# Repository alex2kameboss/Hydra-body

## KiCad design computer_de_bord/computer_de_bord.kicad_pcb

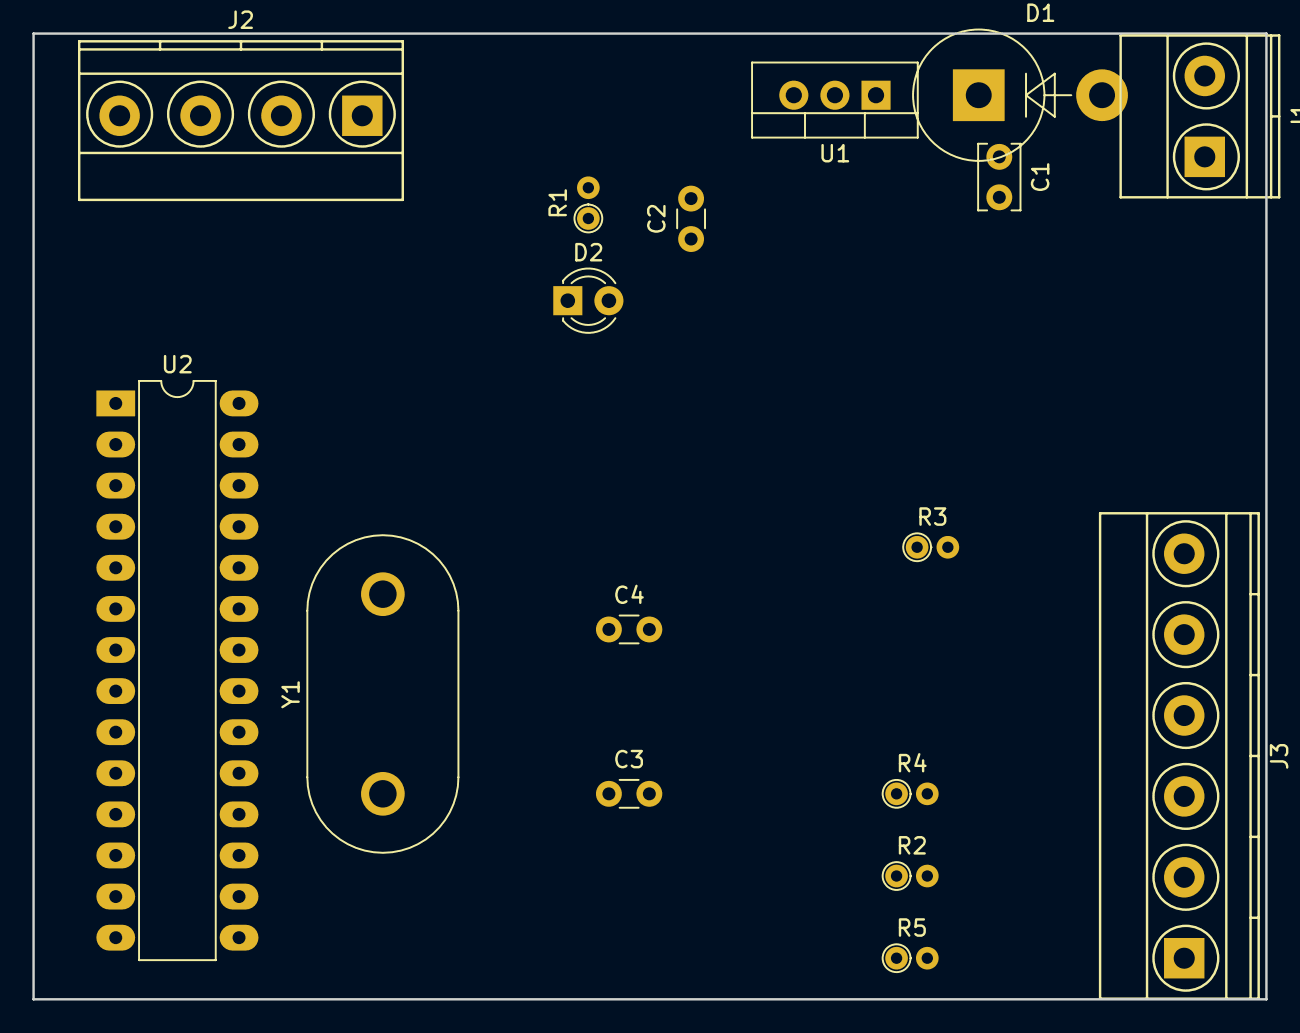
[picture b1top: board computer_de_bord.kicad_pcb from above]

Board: 2 copper layers, 76.2 x 59.7 mm, 17 parts (0 on the bottom side), 13 nets, no tracks yet.

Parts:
C1: 330nF; C_Rect_L4.0mm_W2.5mm_P2.50mm
C2: 100nF; C_Disc_D3.0mm_W1.6mm_P2.50mm
C3, C4: 22pF; C_Disc_D3.0mm_W1.6mm_P2.50mm
D1: 1N4007; D_5KPW_P7.62mm_Vertical_AnodeUp
D2: LED; LED_D3.0mm
J1: Alimentare(+,-); TerminalBlock_Pheonix_MKDS1.5-2pol
J2: Con. LCD(-,+,SDA,SCL); TerminalBlock_Pheonix_MKDS1.5-4pol
J3: Con. externi(+,-,-,+,+,-); TerminalBlock_Pheonix_MKDS1.5-6pol
R1: 220; R_Axial_DIN0204_L3.6mm_D1.6mm_P1.90mm_Vertical
R2: 10k; R_Axial_DIN0204_L3.6mm_D1.6mm_P1.90mm_Vertical
R3, R4, R5: 100k; R_Axial_DIN0204_L3.6mm_D1.6mm_P1.90mm_Vertical
U1: LM7805; TO-220_Vertical
U2: ATMEGA328P-PU; DIP-28_W7.62mm_LongPads
Y1: 16MHz; Crystal_HC33-U_Vertical

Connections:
unnamed: C1.1, D1.1
unnamed: C1.2, C2.2, C3.1, C4.1, D2.1, J1.2, J2.1, J3.2, R2.2, R3.2, R4.2, U2.8, U2.22
unnamed: C2.1, J2.2, J3.4, J3.5, R1.1, U2.7, U2.20
unnamed: C3.2, U2.9, Y1.1
unnamed: C4.2, U2.10, Y1.2
unnamed: D1.2, J1.1
unnamed: D2.2, R1.2
unnamed: J2.3, U2.27
unnamed: J2.4, U2.28
unnamed: J3.1, R5.1
unnamed: J3.3, R4.1, U2.24
unnamed: J3.6, R3.1, U2.25
unnamed: R2.1, R5.2, U2.23

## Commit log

2017-08-23 fisiere masina
2017-08-28 caroserie buna
2017-08-28 caroserie taiata
2017-08-30 caroserie finala taiata in bucati
2017-09-01 ultima caroserie
2017-09-11 fisiere computer de bord
2018-11-13 Ultimii bearings
